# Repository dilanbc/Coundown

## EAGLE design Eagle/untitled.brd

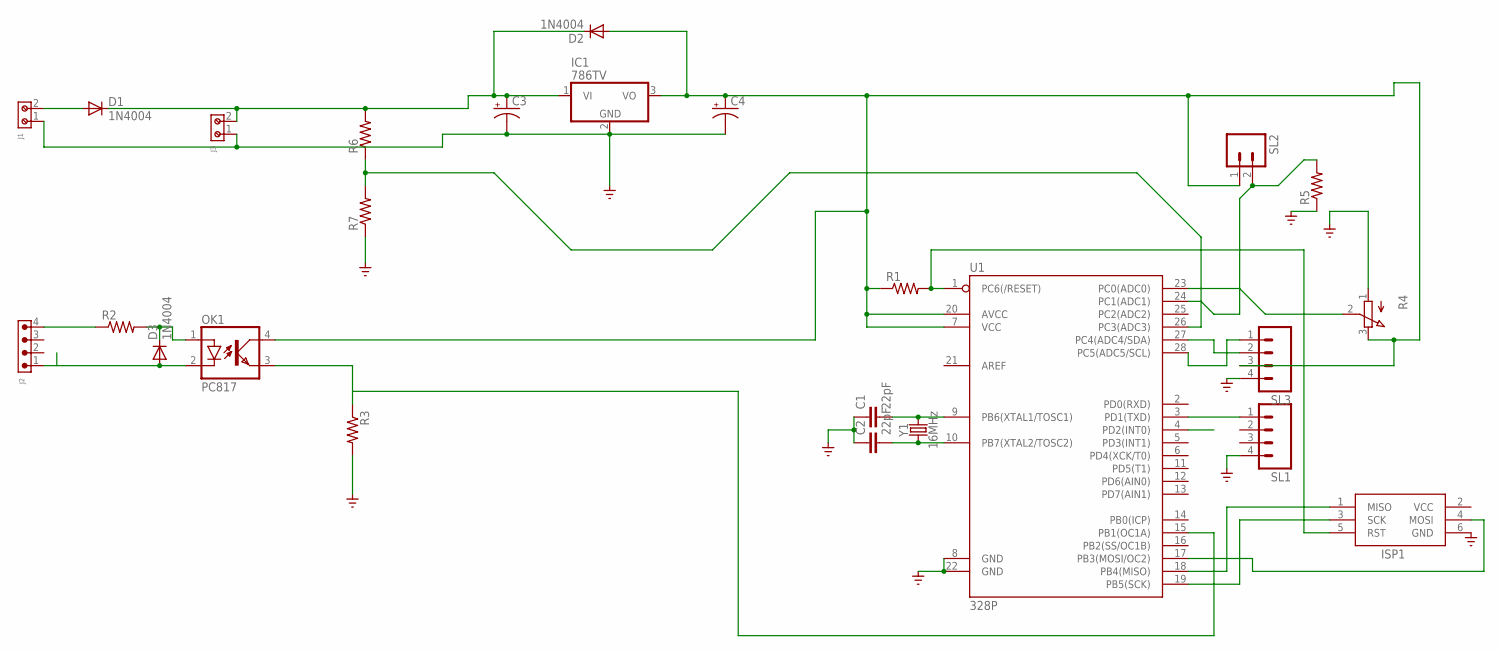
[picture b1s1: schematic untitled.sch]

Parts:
C1, C2: 22pF; CAP-PTH-2.54
C3: CAPACITOR-PE5-10.5; E5-10,5
C4: CAPACITOR-PE5-6; E5-6
D1, D2, D3: 1N4004; DO41-10
IC1: 786TV; TO220V
ISP1: AVRISP-6; AVRISP
J1, J3: 691213710002
J2: 691305530004
OK1: PC817; DIL04
R1, R2, R3, R5, R6, R7: R-US_0207/9; 0207/9
R4: 3RP/1610N
SL1, SL3: M04; 04P
SL2: M02; 02P
U1: 328P; DIP28
Y1: 16MHz; HC49US

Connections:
GND: C1.1, C2.1, C3.-, C4.-, IC1.2 (GND), ISP1.6 (GND), J1.1, J3.1, R3.2, R4.1 (A), R5.1, R7.1, SL1.4, SL3.4, U1.8 (GND), U1.22 (GND)
unnamed: D1.A, J1.2
unnamed: C3.+, D1.C, D2.C, IC1.1 (VI), J3.2, R6.2
unnamed: C1.2, U1.9 (PB6(XTAL1/TOSC1)), Y1.2
unnamed: ISP1.5 (RST), R1.2, U1.1 (PC6(/RESET))
unnamed: ISP1.1 (MISO), U1.18 (PB4(MISO))
unnamed: C4.+, D2.A, IC1.3 (VO), OK1.4 (COL), R1.1, R4.3 (E), SL2.1, SL3.3, U1.7 (VCC), U1.20 (AVCC)
unnamed: C2.2, U1.10 (PB7(XTAL2/TOSC2)), Y1.1
unnamed: ISP1.3 (SCK), U1.19 (PB5(SCK))
unnamed: ISP1.4 (MOSI), U1.17 (PB3(MOSI/OC2))
unnamed: SL1.1, U1.3 (PD1(TXD))
unnamed: D3.A, J2.1, OK1.2 (C)
unnamed: J2.4, R2.1
unnamed: D3.C, OK1.1 (A), R2.2
unnamed: OK1.3 (EMIT), R3.1, U1.15 (PB1(OC1A))
unnamed: R6.1, R7.2, U1.26 (PC3(ADC3))
unnamed: R4.2 (S), U1.23 (PC0(ADC0))
unnamed: R5.2, SL2.2, U1.24 (PC1(ADC1))
unnamed: SL3.2, U1.27 (PC4(ADC4/SDA))
unnamed: SL3.1, U1.28 (PC5(ADC5/SCL))
VCC: ISP1.2 (VCC)

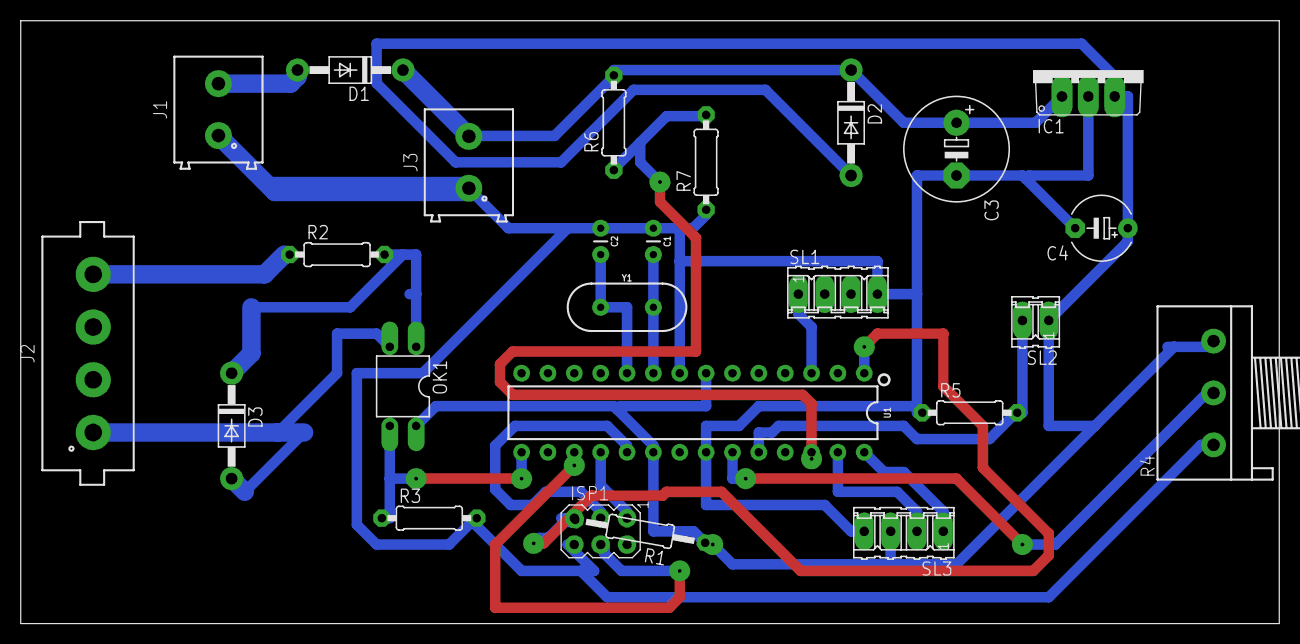
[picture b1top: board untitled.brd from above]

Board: 2 copper layers, 121.3 x 58.1 mm, 25 parts (0 on the bottom side), 20 nets.

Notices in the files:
parts and their libraries:
SparkFun-Capacitors: Licensing: Creative Commons ShareAlike 4.0 International - https://creativecommons.org/licenses/by-sa/4.0
Wurth_Connectors_WR-TBL Rising Cage Clam: Copyright: Würth Elektronik
